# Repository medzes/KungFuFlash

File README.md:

# Kung Fu Flash
Cartridge for the Commodore 64 that packs a punch.

Kung Fu Flash can emulate different cartridge types, load PRG files and use D64 disk images.
Just place your desired CRT, PRG or D64 files on a FAT formatted microSD card and use the built-in launcher to execute them.

This version is cloned from KimJorgensen/KungFuFlash, and has the following changes:
- Replaced LQFP-64 by LQFP-100 version, allowing for STM32F405RG or STM32F407VG. Probably compatible with a STM32H7 400Mhz part too.
- Kim tells me you do need to select a 1MB flash version (RG or VG) for full functionality.
- I replaced the 2 resitor networks by 8 SMD resistors (separate is cheaper at jclpcb)
- I added the DMA pin to PD0.
- Todo: plenty of gpios to be connected to IEC, Tape, LCD, and so on.

## Hardware
There are three buttons on the cartridge; a reset button, a menu button for starting the launcher, and a special button that is used by the freezer cartridges.

The PCB will fit the Stumpy Cartridge Case from TFW8b, you just need to drill some holes for the buttons and make a cut for the microSD card.
If you have mounted the USB connector you will need to cut a hole for that as well.

You can also 3D print a cartridge case as the one designed by bigby, [see here](https://www.thingiverse.com/thing:4153414).

The gerber files and BOM can be found [here](https://github.com/KimJorgensen/KungFuFlash/releases/tag/rev.2).

## Supported Cartridges
The following cartridge types are currently supported:

* Normal cartridge (8k, 16k, Ultimax)
* Action Replay v4.x/v5/v6
* KCS Power Cartridge
* Final Cartridge III(+)
* Simons' BASIC
* Fun Play, Power Play
* Ocean type 1
* Epyx Fastload
* C64 Game System, System 3
* WarpSpeed
* Dinamic
* Zaxxon, Super Zaxxon
* Magic Desk, Domark, HES Australia
* Super Snapshot v5
* Comal-80
* EasyFlash
* Freeze Frame
* Freeze Machine

## Supported File Types
The following file types are currently supported:

* Cartridge (CRT)
* Disk image (D64, D71, D81)
* Program (PRG, P00)
* Firmware update (UPD)

## USB Port
The USB port is active while the launcher is running allowing programs to be transferred from a PC using the EasyFlash 3 USB protocol.
Kung Fu Flash shows up as a standard serial port when connected to a PC not requiring any custom drivers to be installed.
This means, however, that the program on the PC side must be modified to support Kung Fu Flash.
For that reason a modified version of [EasyFlash 3 USB Utilities](3rd_party/ef3utils) has been included in this repository.

## Firmware Update
Just place the KungFuFlash_v1.xx.upd file on the SD card and select the file in the launcher to initiate the firmware update.
The newest firmware can be found [here](https://github.com/KimJorgensen/KungFuFlash/releases/).

For initial firmware installation, [see here](firmware/README.md).

## Limitations
Kung Fu Flash is a so called Software Defined Cartridge where a fast microcontroller emulates cartridge hardware in software.
This makes it extremely flexible, allowing different cartridge types to be supported at a relative low cost.

However, it can be challenging to get the C64 bus timing correct in software and in some places the timing is very close to the limit.
Even though Kung Fu Flash has been tested on different models of the Commodore 64, there is a chance that it doesn't work correctly on your specific model.
Use it at your own risk!

Kung Fu Flash will work with the PAL version of the Commodore 64 or Commodore 128. Support for the NTSC version is still considered experimental.

Disk drive emulation is using kernal vectors and will not work with fast loaders or software that uses direct hardware access which a lot of games does. Currently REL files are not supported and there is only limited write support.

## Thanks
Kung Fu Flash was based on or uses other open source projects:

* [EasyFlash 3](https://bitbucket.org/skoe/easyflash) by Thomas Giesel
* [Draco Browser](https://csdb.dk/release/?id=89910) by Sascha Bader
* [fatfs-stm32](https://github.com/colosimo/fatfs-stm32) by Aurelio Colosimo
* [FatFs](http://elm-chan.org/fsw/ff/00index_e.html) by ChaN
* [libusb_stm32](https://github.com/dmitrystu/libusb_stm32) by Dmitry Filimonchuk
* [stm32f4-bare-metal](https://github.com/fcayci/stm32f4-bare-metal) by Furkan Cayci
* [OpenC64Cart](https://github.com/SukkoPera/OpenC64Cart) by Giorgioggì
* [EasyFlash 3 USB Utilities](https://csdb.dk/release/?id=150097) by Tomaz Kac
* [Disk2easyflash](https://csdb.dk/release/?id=150323) by ALeX Kazik

and a few others. Please check the individual files for their license.

Thanks to Bjørn N. Jørgensen for giving this project its name.

Special thanks to the author of [Sidekick64](https://github.com/frntc/Sidekick64) Carsten Dachsbacher for his support and inspiration.

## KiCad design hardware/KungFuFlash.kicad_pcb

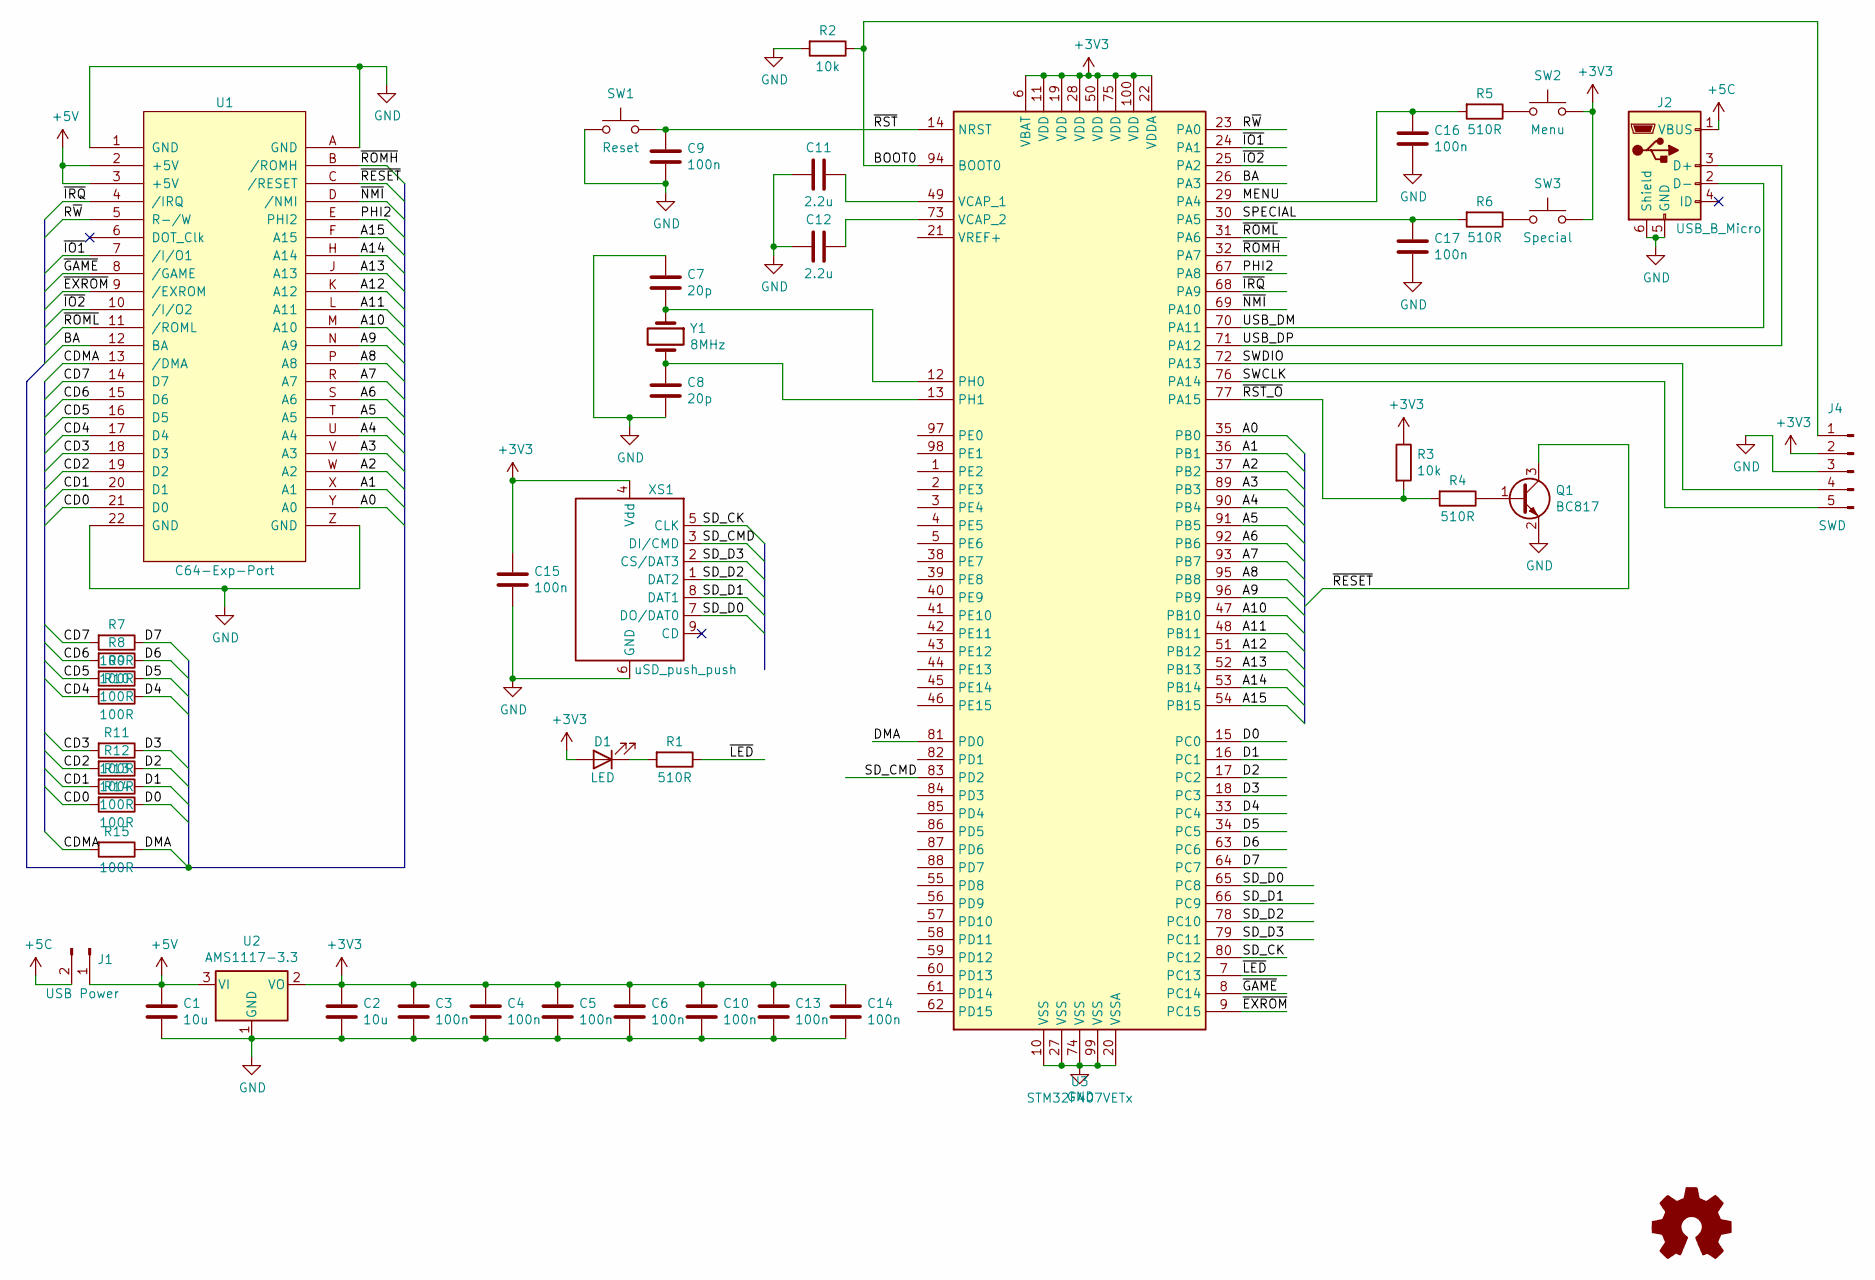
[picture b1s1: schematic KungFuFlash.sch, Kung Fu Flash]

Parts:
C1, C2: 10u; C_0805_2012Metric_Pad1.15x1.40mm_HandSolder
C3, C4, C5, C6, C9, C10, C13, C14, C15, C16, C17: 100n; C_0603_1608Metric_Pad1.05x0.95mm_HandSolder
C7, C8: 20p; C_0603_1608Metric_Pad1.05x0.95mm_HandSolder
C11, C12: 2.2u; C_0805_2012Metric_Pad1.15x1.40mm_HandSolder
D1: LED; LED_0805_2012Metric_Pad1.15x1.40mm_HandSolder
J1: USB Power; PinHeader_1x02_P2.54mm_Vertical
J2: USB_B_Micro; Conn_USBmicro-B_ebay-side_TH
J4: SWD; PinHeader_1x05_P2.54mm_Vertical
Q1: BC817; SOT-23
R1, R4, R5, R6: 510R; R_0805_2012Metric_Pad1.15x1.40mm_HandSolder
R2, R3: 10k; R_0805_2012Metric_Pad1.15x1.40mm_HandSolder
R7, R8, R9, R10, R11, R12, R13, R14, R15: 100R; R_0603_1608Metric_Pad0.98x0.95mm_HandSolder
SW1: Reset; SW_PUSH_6mm_H8mm
SW2: Menu; SW_PUSH_6mm_H8mm
SW3: Special; SW_PUSH_6mm_H8mm
U1: C64-Exp-Port; C64-Cart
U2: AMS1117-3.3; SOT-223-3_TabPin2
U3: STM32F407VETx; LQFP-100_14x14mm_P0.5mm
XS1: uSD_push_push; Conn_uSDcard
Y1: 8MHz; Crystal_SMD_5032-2Pin_5.0x3.2mm

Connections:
+3V3: C2.1, C3.1, C4.1, C5.1, C6.1, C10.1, C13.1, C14.1, C15.1, D1.2 (A), J4.2, R3.1, SW2.1, SW3.1, U2.2 (VO), U3.6 (VBAT), U3.11 (VDD), U3.19 (VDD), U3.22 (VDDA), U3.28 (VDD), U3.50 (VDD), U3.75 (VDD), U3.100 (VDD), XS1.4 (Vdd)
+5C: J1.2, J2.1 (VBUS)
+5V: C1.1, J1.1, U1.2 (+5V), U1.3 (+5V), U2.3 (VI)
/A0: U1.Y (A0), U3.35 (PB0)
/A1: U1.X (A1), U3.36 (PB1)
/A2: U1.W (A2), U3.37 (PB2)
/A3: U1.V (A3), U3.89 (PB3)
/A4: U1.U (A4), U3.90 (PB4)
/A5: U1.T (A5), U3.91 (PB5)
/A6: U1.S (A6), U3.92 (PB6)
/A7: U1.R (A7), U3.93 (PB7)
/A8: U1.P (A8), U3.95 (PB8)
/A9: U1.N (A9), U3.96 (PB9)
/A10: U1.M (A10), U3.47 (PB10)
/A11: U1.L (A11), U3.48 (PB11)
/A12: U1.K (A12), U3.51 (PB12)
/A13: U1.J (A13), U3.52 (PB13)
/A14: U1.H (A14), U3.53 (PB14)
/A15: U1.F (A15), U3.54 (PB15)
/BA: U1.12 (BA), U3.26 (PA3)
/BOOT0: J4.1, R2.1, U3.94 (BOOT0)
/CD0: R14.2, U1.21 (D0)
/CD1: R13.2, U1.20 (D1)
/CD2: R12.2, U1.19 (D2)
/CD3: R11.2, U1.18 (D3)
/CD4: R10.2, U1.17 (D4)
/CD5: R9.2, U1.16 (D5)
/CD6: R8.2, U1.15 (D6)
/CD7: R7.2, U1.14 (D7)
/CDMA: R15.2, U1.13 (/DMA)
/D0: R14.1, U3.15 (PC0)
/D1: R13.1, U3.16 (PC1)
/D2: R12.1, U3.17 (PC2)
/D3: R11.1, U3.18 (PC3)
/D4: R10.1, U3.33 (PC4)
/D5: R9.1, U3.34 (PC5)
/D6: R8.1, U3.63 (PC6)
/D7: R7.1, U3.64 (PC7)
/DMA: R15.1, U3.81 (PD0)
/MENU: C16.1, R5.2, U3.29 (PA4)
/PHI2: U1.E (PHI2), U3.67 (PA8)
/R~W: U1.5 (R-/W), U3.23 (PA0)
/SD_CK: U3.80 (PC12), XS1.5 (CLK)
/SD_CMD: U3.83 (PD2), XS1.3 (DI/CMD)
/SD_D0: U3.65 (PC8), XS1.7 (DO/DAT0)
/SD_D1: U3.66 (PC9), XS1.8 (DAT1)
/SD_D2: U3.78 (PC10), XS1.1 (DAT2)
/SD_D3: U3.79 (PC11), XS1.2 (CS/DAT3)
/SPECIAL: C17.1, R6.2, U3.30 (PA5)
/SWCLK: J4.5, U3.76 (PA14)
/SWDIO: J4.4, U3.72 (PA13)
/USB_DM: J2.2 (D-), U3.70 (PA11)
/USB_DP: J2.3 (D+), U3.71 (PA12)
/~EXROM: U1.9 (/EXROM), U3.9 (PC15)
/~GAME: U1.8 (/GAME), U3.8 (PC14)
/~IO1: U1.7 (/I/O1), U3.24 (PA1)
/~IO2: U1.10 (/I/O2), U3.25 (PA2)
/~IRQ: U1.4 (/IRQ), U3.68 (PA9)
/~LED: R1.1, U3.7 (PC13)
/~NMI: U1.D (/NMI), U3.69 (PA10)
/~RESET: Q1.3 (C), U1.C (/RESET)
/~ROMH: U1.B (/ROMH), U3.32 (PA7)
/~ROML: U1.11 (/ROML), U3.31 (PA6)
/~RST: C9.1, SW1.2, U3.14 (NRST)
/~RST_O: R3.2, R4.2, U3.77 (PA15)
GND: C1.2, C2.2, C3.2, C4.2, C5.2, C6.2, C7.1, C8.2, C9.2, C10.2, C11.1, C12.2, C13.2, C14.2, C15.2, C16.2, C17.2, J2.5 (GND), J2.6 (Shield), J4.3, Q1.2 (E), R2.2, SW1.1, U1.1 (GND), U1.22 (GND), U1.A (GND), U1.Z (GND), U2.1 (GND), U3.10 (VSS), U3.20 (VSSA), U3.27 (VSS), U3.74 (VSS), U3.99 (VSS), XS1.6 (GND)
unnamed: C7.2, U3.12 (PH0), Y1.1
unnamed: C8.1, U3.13 (PH1), Y1.2
unnamed: C11.2, U3.49 (VCAP_1)
unnamed: C12.1, U3.73 (VCAP_2)
unnamed: D1.1 (K), R1.2
unnamed: Q1.1 (B), R4.1
unnamed: R5.1, SW2.2
unnamed: R6.1, SW3.2

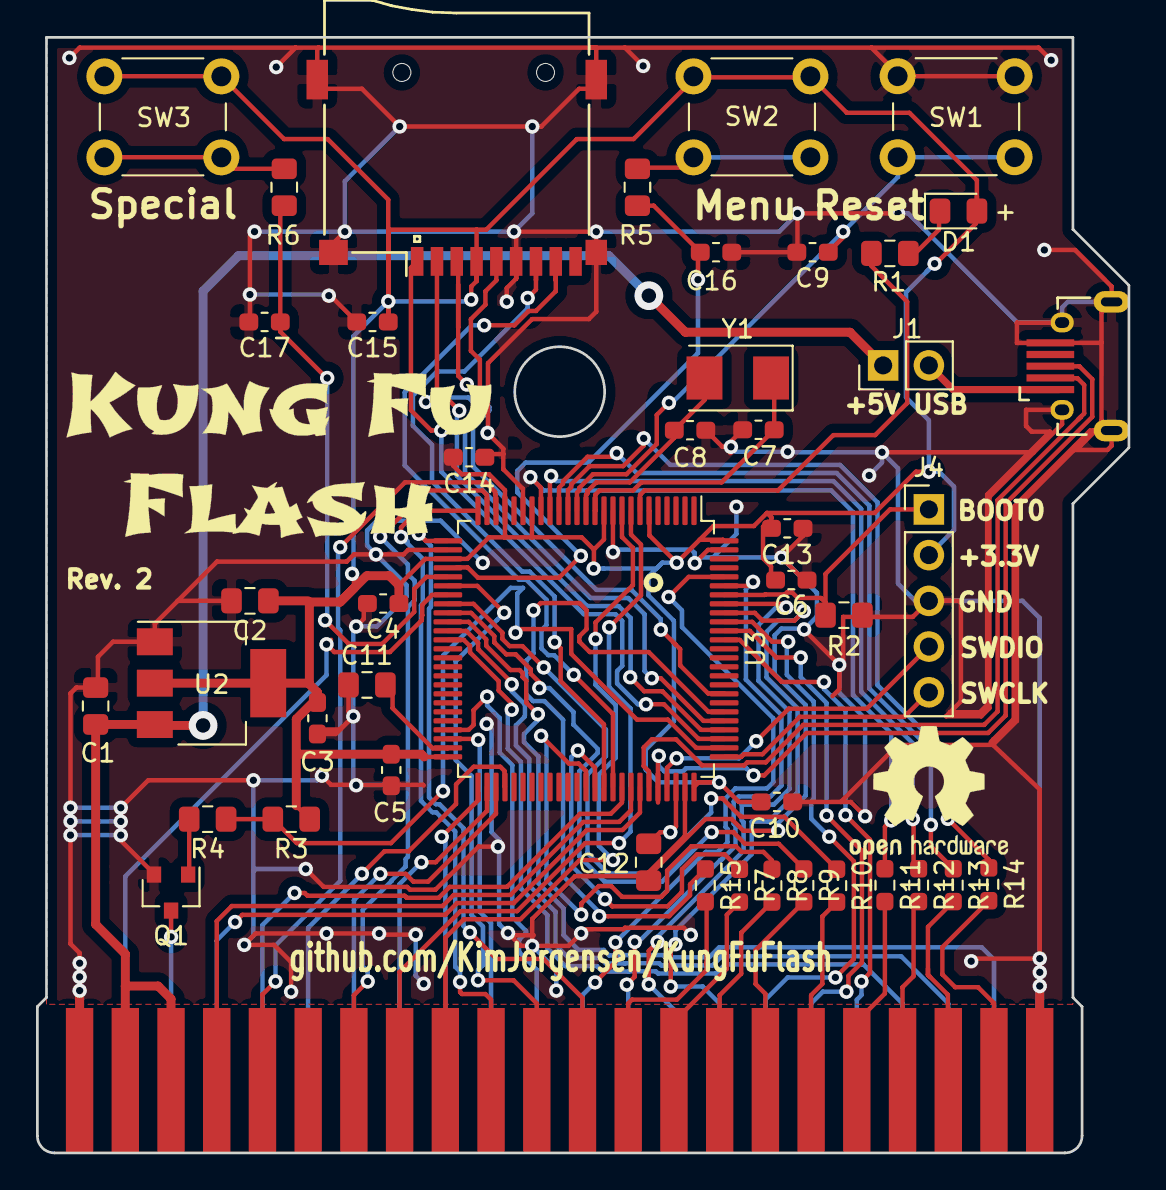
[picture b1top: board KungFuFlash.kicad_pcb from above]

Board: 2 copper layers, 60.6 x 62.0 mm, 45 parts (0 on the bottom side), 74 nets.

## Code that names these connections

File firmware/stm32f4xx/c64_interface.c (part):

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 * for the KungFuFlash rev.2 PCB and the DEVEBOX prototype from the Makefile.
 * Furthermore, the Timer 1 interrupt time position is split into Kernal mode and non-Kernal mode for easier modification.
 * 
 * The DEVEBOX comes with a LED on PA1. That's on a different GPIO bank than the other control signals on PD. 
 * For DEVEBOX the led is only toggled in non-critical code sections.
 * 
 * DEVEBOX uses PD8-PD15 for the databus. This is just as fast for access, as long as it is accessed with ldrb/strb.
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// The following definition forces reliable gcc code inlining when compiling with -Os.
#define INLINE inline __attribute__((always_inline))

#define MENU_RAM_SIGNATURE  "KungFu:Menu"

#ifdef DEVEBOX
#define GPIO_ADDRESSBUS GPIOE
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}

/*************************************************
* C64 address bus on PB0-PB15 (or PE0-PE15)
* Returned as 32 bit value for performance
*************************************************/
static INLINE uint32_t c64_addr_read()
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}

/*************************************************
* C64 data bus on PC0-PC7 (or PD8-PD15)
* Returned as 32 bit value for performance
*************************************************/
static INLINE uint32_t c64_data_read()
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
static INLINE void c64_data_write(uint8_t data)
{
    // Make PC0-PC7 (or PD8-15) output
    *((volatile uint16_t *)&GPIO_DATABUS->MODER + GPIO_DATABUS_LANE) = 0x5555;

    *((volatile uint8_t *)&GPIO_DATABUS->ODR + GPIO_DATABUS_LANE) = data;
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
static INLINE void c64_data_input(void)
{
    // Make PC0-PC7 (or PD8-15) input
    *((volatile uint16_t *)&GPIO_DATABUS->MODER + GPIO_DATABUS_LANE) = 0x0000;
    __DMB();
}

static void c64_data_config(void)
{
    // Make PC0-PC7 (or PD8-15) input
    c64_data_input();
}

/*************************************************
* C64 control bus on PA0-PA3 and PA6-PA7 (or PC0-4,PC6-PC7,PC13)
* Menu button & special button on PA4 & PA5 (or PC4, PC5)
* Returned as 32 bit value for performance
*************************************************/
#ifdef DEVEBOX
#define GPIO_CONTROL GPIOC
#define C64_WRITE_POS   0    // R/W on PC0
#define C64_IO1_POS     1    // IO1 on PC1
#define C64_IO2_POS     2    // IO2 on PC2
#define C64_BA_POS      3    // BA on PC3
#define MENU_BTN_POS    4    // Menu button on PC4, to be compatible with the EXTI4 code.
#define SPECIAL_BTN_POS 13   // Special button on PC13
#define C64_ROML_POS    6    // ROML on PC6
#define C64_ROMH_POS    7    // ROMH on PC7
#define MENU_BTN_INT_PORT SYSCFG_EXTICR2_EXTI4_PC
#else
#define GPIO_CONTROL GPIOA
#define C64_WRITE_POS   0    // R/W on PA0
#define C64_IO1_POS     1    // IO1 on PA1
#define C64_IO2_POS     2    // IO2 on PA2
#define C64_BA_POS      3    // BA on PA3
#define MENU_BTN_POS    4    // Menu button on PA4
#define SPECIAL_BTN_POS 5    // Special button on PA5
#define C64_ROML_POS    6    // ROML on PA6
#define C64_ROMH_POS    7    // ROMH on PA7
#define MENU_BTN_INT_PORT SYSCFG_EXTICR2_EXTI4_PA
#endif
#define C64_WRITE   (1UL<<C64_WRITE_POS)
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
static void c64_control_config(void)
{
    // Make PA0-PA3 and PA6-PA7 input (or PC0-4, PC6-7, PC13)
    GPIO_CONTROL->MODER &= ~(
      (3UL<<C64_WRITE_POS*2) |
      (3UL<<C64_IO1_POS*2) |
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}

/*************************************************
* C64 GAME and EXROM on PC14 & PC15 (or PD0-1,PD2)
* Status LED on PC13 (or PA1)
*************************************************/

#ifdef DEVEBOX
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#define C64_DMA_POS     3

#define GPIO_STATUS_LED    GPIOA
// Status led on PA1 can't be written at the same time as GAME/EXROM on PD. 
// So for DEVEBOX the STATUS_LED_ON/STATUS_LED_OFF macros do nothing.
#define STATUS_LED_ON      (0)
#define STATUS_LED_OFF     (0)
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#define C64_EXROM_LOW   GPIO_BSRR_BR15
#define C64_GAME_POS    14
#define C64_EXROM_POS   15
// DMA pin is not supported on pcb rev2.
#define C64_DMA_HIGH    (0)
#define C64_DMA_LOW     (0)
#define C64_DMA_POS     -1
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    led_off();
    c64_crt_control(C64_GAME_HIGH | C64_EXROM_HIGH | C64_DMA_HIGH);

    // Set PC14 & PC15 (or PD0,PD1,PD3) as open-drain
    GPIO_OTHER->OTYPER |= 
     (1UL<<C64_GAME_POS) |
     (1UL<<C64_EXROM_POS) |
     ((C64_DMA_POS>=0) ? (1UL<<C64_DMA_POS) : 0);

    // Set PC13-PC15 (or PD0,PD1,PD3, PA1) as output 
    MODIFY_REG(GPIO_STATUS_LED->MODER, (3UL<<STATUS_LED_POS*2), (1UL<<STATUS_LED_POS*2));
    MODIFY_REG(GPIO_OTHER->MODER,
        (3UL<<C64_GAME_POS*2) |
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}

/*************************************************
* C64 IRQ and NMI on PA9 & PA10 (or PD4,PD5)
*************************************************/
#ifdef DEVEBOX
#define GPIO_INTERRUPT GPIOD
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{
    c64_irq_nmi(C64_IRQ_NMI_HIGH);

    // Set PA9 & PA10 (or PD4, PD5) as open-drain
    GPIO_INTERRUPT->OTYPER |= (
      (1UL<<C64_IRQ_POS) |
      (1UL<<C64_NMI_POS)
    );

    // Set PA9 & PA10 (or PD4, PD5) as output
    MODIFY_REG(GPIO_INTERRUPT->MODER, 
      (3UL<<C64_IRQ_POS*2) | 
      (3UL<<C64_NMI_POS*2),
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}

/*************************************************
* C64 clock input on PA8 (timer 1)
* C64 clock is 0.985 MHz (PAL) / 1.023 MHz (NTSC)
*************************************************/
static void c64_clock_config()
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    RCC->APB2ENR |= RCC_APB2ENR_TIM1EN;
    __DSB();

    // Set PA8 as alternate mode 1 (TIM1_CH1)
    MODIFY_REG(GPIOA->AFR[1], GPIO_AFRH_AFSEL8, GPIO_AFRH_AFSEL8_0);
    MODIFY_REG(GPIOA->MODER, GPIO_MODER_MODER8, GPIO_MODER_MODER8_1);

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}

/*************************************************
* C64 reset on PA15 (or PD6)
* Reset is inverted externally with a drive transistor in PCB rev2. Reset is not inverted in DEVEBOX.
*************************************************/
#ifdef DEVEBOX
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		);
	}

    // Set PA15 (or PD6) as output
    MODIFY_REG(GPIO_RESET->MODER, 
       (3UL << C64_RESET_POS*2),
       (1UL << C64_RESET_POS*2)
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}

/*************************************************
* Menu button and special button on PA4 & PA5
*************************************************/

static INLINE bool menu_button(void)
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
static void button_config(void)
{
    // Make PA4 and PA5 (or PC4,PC13) input
    GPIO_CONTROL->MODER &= ~(
      (3UL<<MENU_BTN_POS*2)|
      (3UL<<SPECIAL_BTN_POS*2)
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      (2UL<<SPECIAL_BTN_POS*2)
    );
    
    // Enable EXTI4 interrupt on PA4 (or PC4)
    MODIFY_REG(SYSCFG->EXTICR[1], SYSCFG_EXTICR2_EXTI4, MENU_BTN_INT_PORT);
    EXTI->IMR |= EXTI_IMR_MR4;

    // Rising edge trigger on PA4 (or PC4)
    EXTI->RTSR |= EXTI_RTSR_TR4;
    EXTI->FTSR &= ~EXTI_FTSR_TR4;

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
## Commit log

2020-12-18 Change to LQFP-100, replace resitor network, add DMA
2021-01-17 DEVEBOX development board pinout support
2021-02-11 Add soft-kernal mode support. Tested on DEVEBOX

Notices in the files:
firmware/stm32f4xx/c64_interface.c:
Copyright (c) 2019-2021 Kim Jørgensen, Marko Edzes
